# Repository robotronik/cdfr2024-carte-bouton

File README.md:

Dépôt récupéré sans accroc, je mettrais ici des notes sur mon avancement.

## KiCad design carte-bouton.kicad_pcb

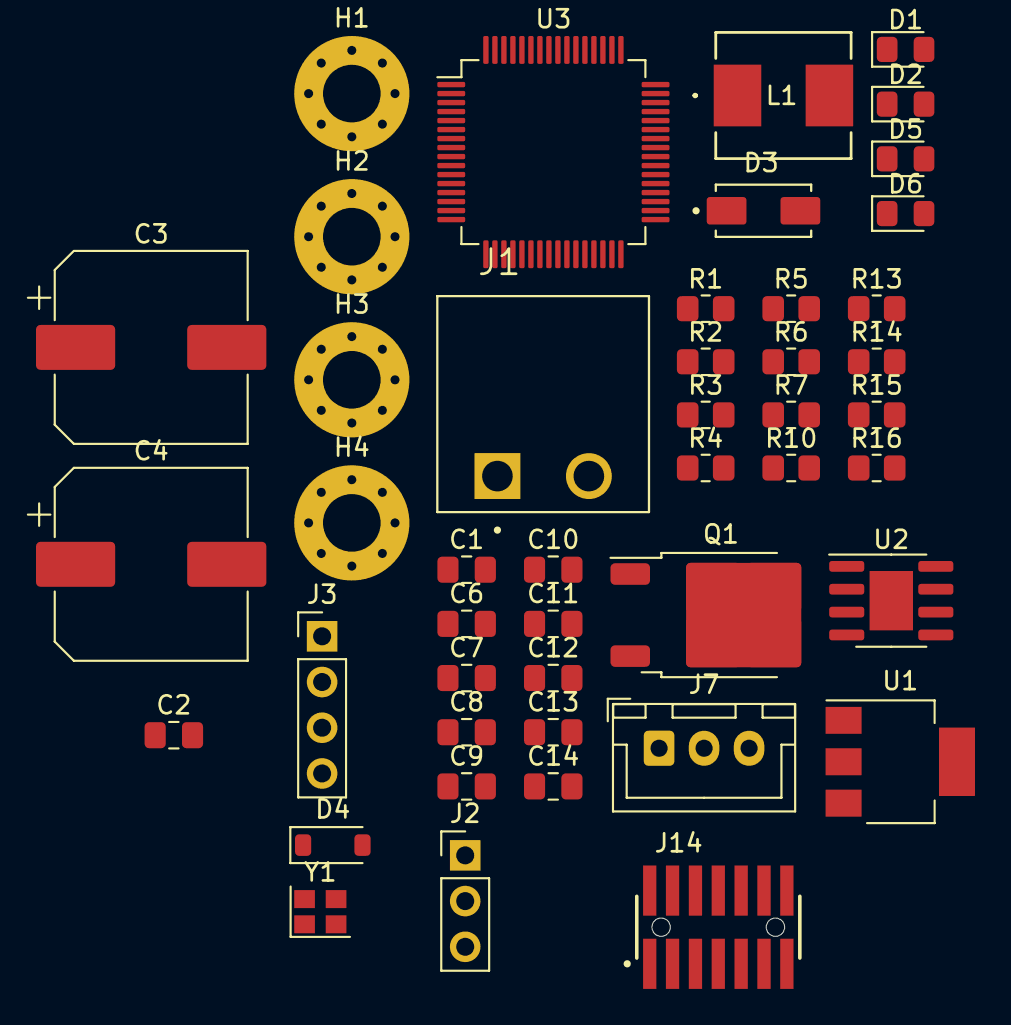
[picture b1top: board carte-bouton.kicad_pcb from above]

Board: 2 copper layers, 46 parts (0 on the bottom side), 29 nets, no tracks yet.

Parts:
C1, C6, C7, C8, C9: 100nF; C_0805_2012Metric_Pad1.18x1.45mm_HandSolder
C2: 10uF; C_0805_2012Metric_Pad1.18x1.45mm_HandSolder
C3: 470uF; CP_Elec_10x10.5
C4: 220uF; CP_Elec_10x10.5
C10: 4.7uF; C_0805_2012Metric_Pad1.18x1.45mm_HandSolder
C11: 10nF; C_0805_2012Metric_Pad1.18x1.45mm_HandSolder
C12: 1uF; C_0805_2012Metric_Pad1.18x1.45mm_HandSolder
C13, C14: 10pF; C_0805_2012Metric_Pad1.18x1.45mm_HandSolder
D1, D2, D5, D6: LED; LED_0805_2012Metric_Pad1.15x1.40mm_HandSolder
D3: DIODE; DIOM505270X240
D4: D_Zener; D_SOD-123
H1, H2, H3, H4: MountingHole_Pad; MountingHole_3.2mm_M3_Pad_Via
J1: Connecteur batterie; CUI_TBP01R1-508-02BE
J2: Conn_01x03; PinHeader_1x03_P2.54mm_Vertical
J3: Conn_01x04; PinHeader_1x04_P2.54mm_Vertical
J7: Conn_01x03; JST_XH_B3B-XH-A_1x03_P2.50mm_Vertical
J14: Conn_ST_STDC14; SAMTEC_FTSH-107-01-L-DV-K-A
L1: 10uH; IND_IHLP_2525_CZ-M
Q1: Q_NMOS_GDS; TO-252-2
R1, R2: 56k; R_0805_2012Metric_Pad1.20x1.40mm_HandSolder
R3, R10, R13, R14: 10k; R_0805_2012Metric_Pad1.20x1.40mm_HandSolder
R4: 2k4; R_0805_2012Metric_Pad1.20x1.40mm_HandSolder
R5, R15, R16: 220; R_0805_2012Metric_Pad1.20x1.40mm_HandSolder
R6: 150; R_0805_2012Metric_Pad1.20x1.40mm_HandSolder
R7: 3k9; R_0805_2012Metric_Pad1.20x1.40mm_HandSolder
U1: LM317_SOT-223; SOT-223-3_TabPin2
U2: LMR16020PDDA; SOIC-8-1EP_3.9x4.9mm_P1.27mm_EP2.41x3.3mm
U3: STM32F401RCTx; LQFP-64_10x10mm_P0.5mm
Y1: Crystal_GND24; Crystal_SMD_2520-4Pin_2.5x2.0mm

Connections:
+3.3V: C2.1, C6.1, C7.1, C8.1, C9.1, C11.1, C12.1, D2.2 (A), J14.3 (VCC), R4.1, U1.2 (VO), U3.1 (VBAT), U3.13 (VREF+), U3.19 (VDD), U3.32 (VDD), U3.48 (VDD), U3.64 (VDD)
+5V: C4.1, D1.2 (A), L1.2, R2.1, U1.3 (VI)
+BATT: C3.1, J1.1, R1.1, U2.2 (VIN), U2.3 (EN)
/I2C_CLK: J7.1, U3.58 (PB6)
/I2C_SDA: J7.2, U3.59 (PB7)
/InputVoltage: J1.2, Q1.2 (D)
GND: C2.2, C3.2, C4.2, C6.2, C7.2, C8.2, C9.2, C10.2, C11.2, C12.2, C13.1, C14.2, D3.1 (K), D4.2 (A), H1.1, H2.1, H3.1, H4.1, J2.3, J3.2, J7.3, J14.5 (GND), J14.7 (GND), Q1.3 (S), R3.2, R5.2, R6.2, R7.2, R10.1, R15.2, R16.2, U2.4 (RT/SYNC), U2.7 (GND), U2.9 (THERMAL_PAD), U3.12 (VSSA), U3.18 (VSS), U3.31 (VSS), U3.47 (VSS), U3.63 (VSS), Y1.2, Y1.4
unnamed: C13.2, R13.1, Y1.3
unnamed: C14.1, R14.1, Y1.1
unnamed: D1.1 (K), R5.1
unnamed: D2.1 (K), R6.1
unnamed: C1.2, D3.2 (A), L1.1, U2.8 (SW)
unnamed: D4.1 (K), Q1.1 (G), R1.2
unnamed: D5.2 (A), U3.45 (PA12)
unnamed: D5.1 (K), R15.1
unnamed: D6.2 (A), U3.50 (PA15)
unnamed: D6.1 (K), R16.1
unnamed: R4.2, R7.1, U1.1 (ADJ)
unnamed: C1.1, U2.1 (BOOT)
unnamed: R2.2, R3.1, U2.5 (FB)
unnamed: R10.2, U3.60 (BOOT0)
unnamed: R13.2, U3.5 (PH0)
unnamed: R14.2, U3.6 (PH1)
unnamed: C10.1, U3.30 (VCAP1)
RST: J3.4, J14.12 (~RST), U3.7 (NRST)
Rx: J2.2, J14.13 (VCP_RX), U3.17 (PA3)
SWCLK: J3.1, J14.6 (JCLK/SWCLK), U3.49 (PA14)
SWDIO: J3.3, J14.4 (JTMS/SWDIO), U3.46 (PA13)
Tx: J2.1, J14.14 (VCP_TX), U3.16 (PA2)

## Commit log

2024-02-26 first git
2024-02-27 Notes d'avancement
2024-03-10 Boutons, LEDs sans ecran
2024-03-11 modification schémas
